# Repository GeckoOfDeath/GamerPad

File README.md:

# GamerPad 👾🕹️
GamerPad is a keyboard design that would allow you to quick chat in games without having to use time consuming text strings.

🔥🔥🔥Description🔥🔥🔥

I worked around 20 hours on the project (missed time on lapis LoL). Even though I had to take a big breakIi think it came out well. I have given it a KWK firmware but small adjustments may be needed after receiving the parts. It will type say "/ hello" on its own so you can avoid all the random "enter" and "/" while gaming!

## Features:
- White PLA case!
- 128x32 OLED Display
- EC11 Rotary encoder for switching modes
- 12 WS2812B RGB LEDs. For Maximum underglow.
- 3 Keys

## CAD Model: 
It friction fits with 2 solid pieces. It has gaps for airflow along with optimal underglow experience without ypur hand falling into it. It uses a organic design to keep a natural atheistic. It can fit into your palm with ease along with being erginomic.

## Firmware Overview
This hackpad uses KMK firmware for everything. 

- the rotary encoder acts as a button. Will change your "mode" in the future.
- The 3 keys currently act as macros.
- The OLED is untested (due to lack of oled) But has been set up!

## Mother Board
Pretty basic, but fun silkscreen!

## BOM:
!!!!!!!!!! EXSTENDED BOM IN PRODUCTION FOLDER !!!!!!!!!!!!!
Here should be everything you need to make this hackpad

- 3x Cherry MX Switches
- 3x DSA Keycaps
- 12x WS2812B LEDs
- 1x 0.91" 128x32 OLED Display
- 1x EC11 Rotary Encoder
- 1x XIAO RP2040
- 1x Case (2 printed parts)

I might add more in the future! That's it for n

Feel Free to build your own. 👷

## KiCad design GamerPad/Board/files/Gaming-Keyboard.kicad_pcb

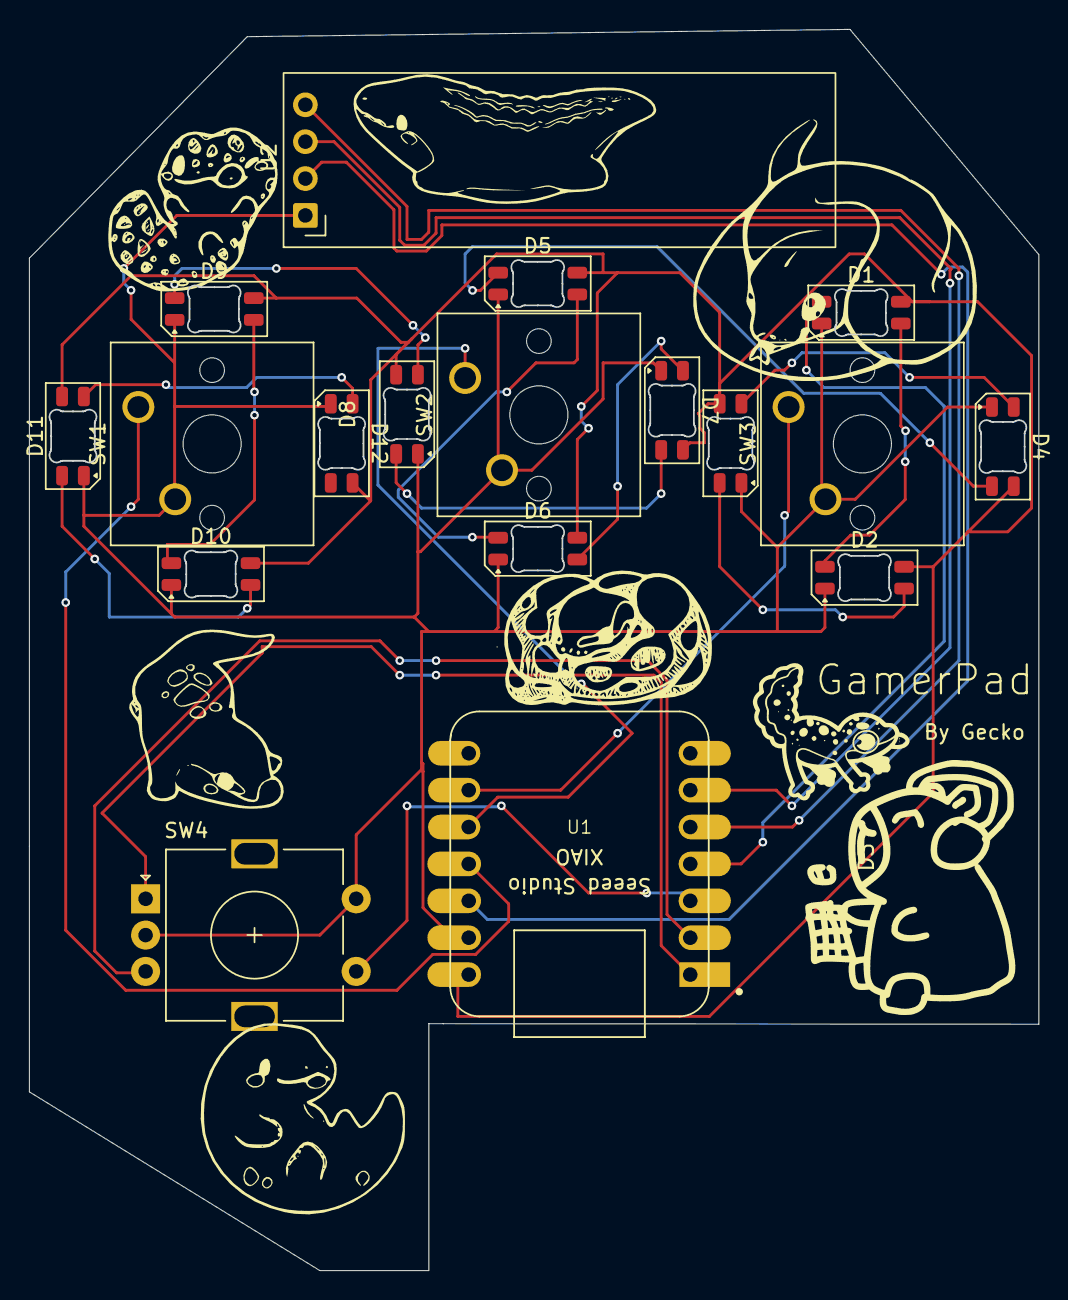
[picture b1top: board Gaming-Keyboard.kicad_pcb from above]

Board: 2 copper layers, 69.5 x 85.5 mm, 18 parts (0 on the bottom side), 23 nets.

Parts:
D1, D2, D3, D4, D5, D6, D7, D8, D9, D10, D11, D12: SK6812MINI-E; LED_SK6812MINI-E_3.2x2.8mm_P1.5mm_ReverseMount
SW1, SW2, SW3: SW_Push; SW_Cherry_MX_1.00u_PCB
SW4: RotaryEncoder_Switch; RotaryEncoder_Alps_EC11E-Switch_Vertical_H20mm
U1: MOUDLE-SEEEDUINO-XIAO; XIAO-Generic-Hybrid-14P-2.54-21X17.8MM
U2: ER_OLEDM0.91_1x-I2C

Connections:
+3V3: U1.12 (3V3), U2.2 (VCC)
+5V: D1.3 (VDD), D2.3 (VDD), D3.3 (VDD), D4.3 (VDD), D5.3 (VDD), D6.3 (VDD), D7.3 (VDD), D8.3 (VDD), D9.3 (VDD), D10.3 (VDD), D11.3 (VDD), D12.3 (VDD), U1.14 (5V)
GND: D1.1 (VSS), D2.1 (VSS), D3.1 (VSS), D4.1 (VSS), D5.1 (VSS), D6.1 (VSS), D7.1 (VSS), D8.1 (VSS), D9.1 (VSS), D10.1 (VSS), D11.1 (VSS), D12.1 (VSS), SW1.2, SW2.2, SW3.2, SW4.C, SW4.S2, U1.13 (GND), U2.1 (GND)
unnamed: D1.2 (DIN), U1.4 (PA11_A3_D3)
unnamed: D1.4 (DOUT), D2.2 (DIN)
unnamed: D2.4 (DOUT), D3.2 (DIN)
unnamed: D3.4 (DOUT), D4.2 (DIN)
unnamed: D4.4 (DOUT), D5.2 (DIN)
unnamed: D5.4 (DOUT), D6.2 (DIN)
unnamed: D6.4 (DOUT), D7.2 (DIN)
unnamed: D7.4 (DOUT), D8.2 (DIN)
unnamed: D8.4 (DOUT), D9.2 (DIN)
unnamed: D9.4 (DOUT), D10.2 (DIN)
unnamed: D10.4 (DOUT), D11.2 (DIN)
unnamed: D11.4 (DOUT), D12.2 (DIN)
unnamed: SW4.A, U1.1 (PA02_A0_D0)
unnamed: SW4.B, U1.2 (PA4_A1_D1)
unnamed: SW2.1, U1.10 (PA5_A9_D9_MISO)
unnamed: SW1.1, U1.11 (PA6_A10_D10_MOSI)
unnamed: SW3.1, U1.9 (PA7_A8_D8_SCK)
unnamed: U1.5 (PA8_A4_D4_SDA), U2.4 (SDA)
unnamed: U1.6 (PA9_A5_D5_SCL), U2.3 (SCL)
unnamed: SW4.S1, U1.3 (PA10_A2_D2)
